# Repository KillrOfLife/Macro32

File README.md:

# Macro32

The Macro32 is a macropad featuring a stm32.
This project was a way for me to learn how to integrate an IC of my choosing on my PCB.
It was also my fist project using kicad

## Take a look

[kicad project](https://kicanvas.org/?github=https://github.com/KillrOfLife/Macro32/blob/main/PCB/macro32.kicad_pro)

## How can I make it myself

Great question!
Go look in the github releases for the latest tag
There you should find the downloads for the PCB production files (aka gerbers)
And the STL's for the case parts if you want that too. (you may need to download the source code)

## How to assemble

For any help assembling this macropad refer to the [build guide](https://github.com/KillrOfLife/Macro32/blob/main/buildguide.md).

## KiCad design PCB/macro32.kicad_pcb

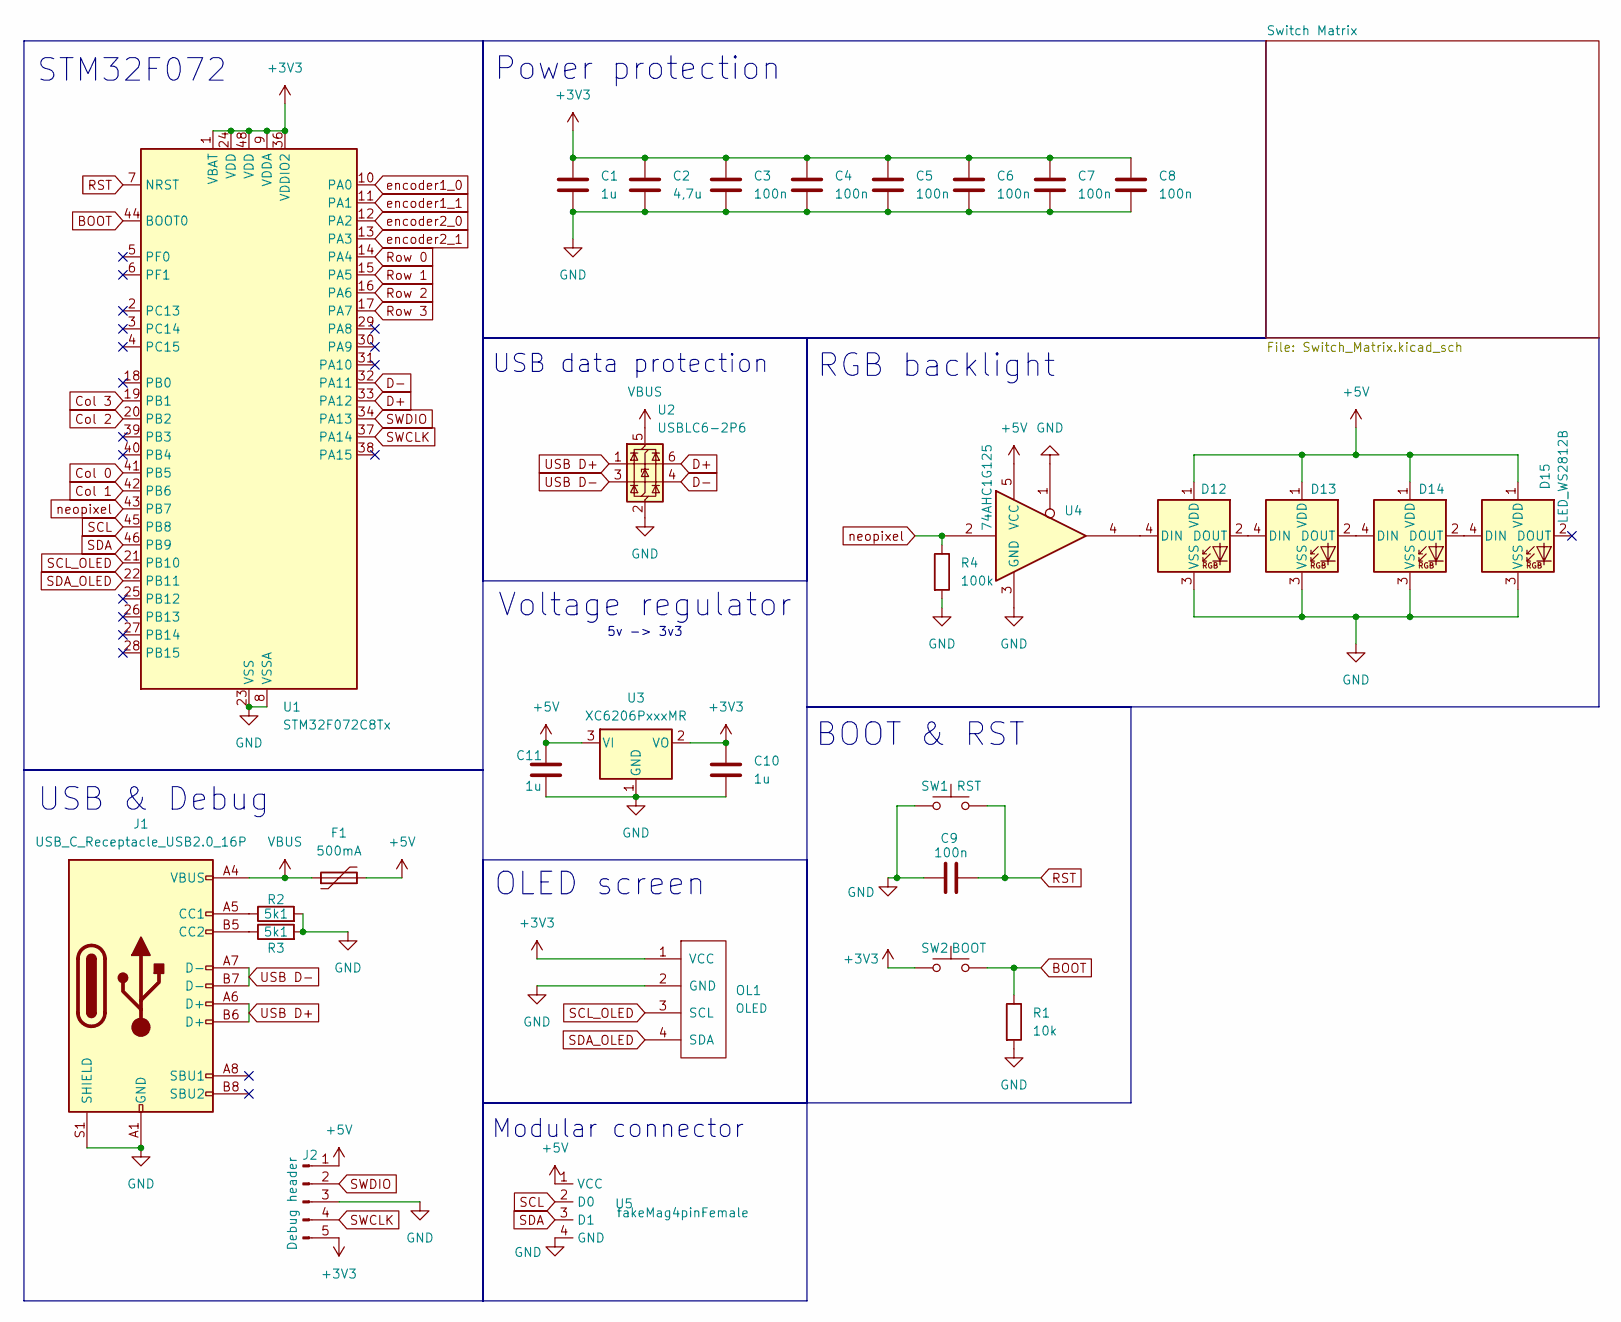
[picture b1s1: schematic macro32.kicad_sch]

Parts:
C1, C10, C11: 1u; LED_0805
C2: 4,7u; LED_0805
C3, C4, C5, C6, C7, C8, C9: 100n; LED_0805
D12, D13, D14, D15: LED_WS2812B
F1: 500mA; Resistor_1206
J1: USB_C_Receptacle_USB2.0_16P; USB_C_Receptacle_GCT_USB4110
J2: Debug header; PinHeader_1x05_P2.54mm_Vertical
OL1: OLED; OLED_128x64
R1: 10k; Resistor_0805
R2, R3: 5k1; Resistor_0805
R4: 100k; Resistor_0805
SW1: RST; SW_SPST_TS-1088-xR020
SW2: BOOT; SW_SPST_TS-1088-xR020
U1: STM32F072C8Tx; LQFP-48_7x7mm_P0.5mm
U2: USBLC6-2P6; SOT-666
U3: XC6206PxxxMR; SOT-23-3
U4: 74AHC1G125; SOT-353_SC-70-5_Handsoldering
U5: fakeMag4pinFemale; fakemag4pin90degFemale

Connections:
+3V3: C1.1, C2.1, C3.1, C4.1, C5.1, C6.1, C7.1, C8.1, C10.1, J2.5, OL1.1 (VCC), SW2.1, U1.1 (VBAT), U1.9 (VDDA), U1.24 (VDD), U1.36 (VDDIO2), U1.48 (VDD), U3.2 (VO)
+5V: C11.1, D12.1 (VDD), D13.1 (VDD), D14.1 (VDD), D15.1 (VDD), F1.2, J2.1, U3.3 (VI), U4.5 (VCC), U5.1 (VCC)
BOOT: R1.1, SW2.2, U1.44 (BOOT0)
Col 0: U1.41 (PB5); also elsewhere on the board
Col 1: U1.42 (PB6); also elsewhere on the board
Col 2: U1.20 (PB2); also elsewhere on the board
Col 3: U1.19 (PB1); also elsewhere on the board
D+: U1.33 (PA12), U2.6 (I/O1)
D-: U1.32 (PA11), U2.4 (I/O2)
GND: C1.2, C2.2, C3.2, C4.2, C5.2, C6.2, C7.2, C8.2, C9.1, C10.2, C11.2, D12.3 (VSS), D13.3 (VSS), D14.3 (VSS), D15.3 (VSS), J1.A1 (GND), J1.A12 (GND), J1.B1 (GND), J1.B12 (GND), J1.S1 (SHIELD), J2.3, OL1.2 (GND), R1.2, R2.2, R3.2, R4.2, SW1.1, U1.8 (VSSA), U1.23 (VSS), U1.35 (VSS), U1.47 (VSS), U2.2 (GND), U3.1 (GND), U4.1, U4.3 (GND), U5.4 (GND); also elsewhere on the board
unnamed: D12.4 (DIN), U4.4
unnamed: D12.2 (DOUT), D13.4 (DIN)
unnamed: D13.2 (DOUT), D14.4 (DIN)
unnamed: D14.2 (DOUT), D15.4 (DIN)
unnamed: J1.A5 (CC1), R2.1
unnamed: J1.B5 (CC2), R3.1
RST: C9.2, SW1.2, U1.7 (NRST)
Row 0: U1.14 (PA4); also elsewhere on the board
Row 1: U1.15 (PA5); also elsewhere on the board
Row 2: U1.16 (PA6); also elsewhere on the board
Row 3: U1.17 (PA7); also elsewhere on the board
SCL: U1.45 (PB8), U5.2 (D0)
SCL_OLED: OL1.3 (SCL), U1.21 (PB10)
SDA: U1.46 (PB9), U5.3 (D1)
SDA_OLED: OL1.4 (SDA), U1.22 (PB11)
SWCLK: J2.4, U1.37 (PA14)
SWDIO: J2.2, U1.34 (PA13)
USB D+: J1.A6 (D+), J1.B6 (D+), U2.1 (I/O1)
USB D-: J1.A7 (D-), J1.B7 (D-), U2.3 (I/O2)
VBUS: F1.1, J1.A4 (VBUS), J1.A9 (VBUS), J1.B4 (VBUS), J1.B9 (VBUS), U2.5 (VBUS)
encoder1_0: U1.10 (PA0); also elsewhere on the board
encoder1_1: U1.11 (PA1); also elsewhere on the board
encoder2_0: U1.12 (PA2); also elsewhere on the board
encoder2_1: U1.13 (PA3); also elsewhere on the board
neopixel: R4.1, U1.43 (PB7), U4.2

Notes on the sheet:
Power protection
STM32F072
5v -> 3v3
RGB backlight
USB & Debug
Modular connector
Voltage regulator
BOOT & RST
OLED screen
USB data protection

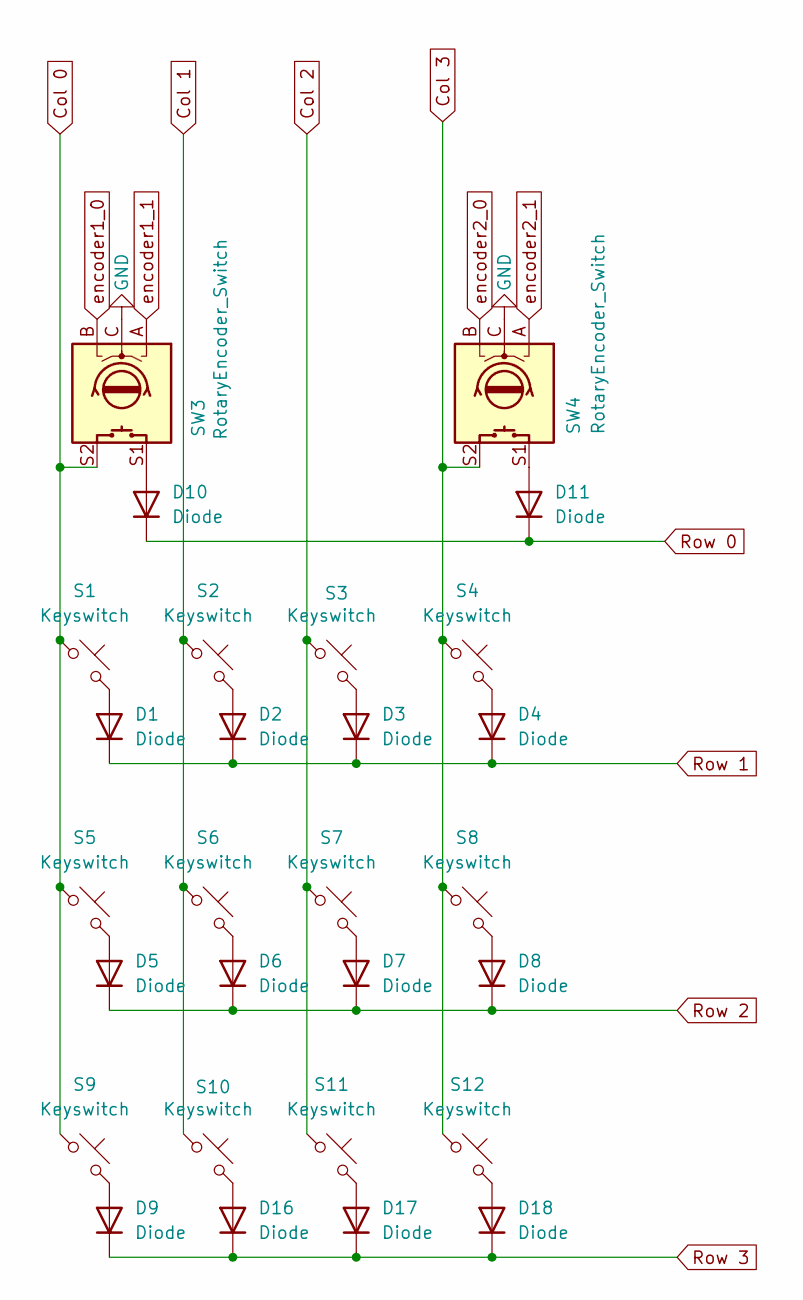
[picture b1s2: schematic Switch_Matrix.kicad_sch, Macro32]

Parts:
D1, D2, D3, D4, D5, D6, D7, D8, D9, D10, D11, D16, D17, D18: Diode; Diode_SOD-123
S1, S2, S3, S4, S5, S6, S7, S8, S9, S10, S11, S12: Keyswitch; Hotswap_MX_1.00u
SW3, SW4: RotaryEncoder_Switch; keyswitch_cherrymx_hotswap_1u_rotary_encoder_ec12

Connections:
Col 0: S1.1, S5.1, S9.1, SW3.S2; also elsewhere on the board
Col 1: S2.1, S6.1, S10.1; also elsewhere on the board
Col 2: S3.1, S7.1, S11.1; also elsewhere on the board
Col 3: S4.1, S8.1, S12.1, SW4.S2; also elsewhere on the board
GND: SW3.C, SW4.C; also elsewhere on the board
unnamed: D1.2 (A), S1.2
unnamed: D2.2 (A), S2.2
unnamed: D3.2 (A), S3.2
unnamed: D4.2 (A), S4.2
unnamed: D5.2 (A), S5.2
unnamed: D6.2 (A), S6.2
unnamed: D7.2 (A), S7.2
unnamed: D8.2 (A), S8.2
unnamed: D9.2 (A), S9.2
unnamed: D10.2 (A), SW3.S1
unnamed: D11.2 (A), SW4.S1
unnamed: D16.2 (A), S10.2
unnamed: D17.2 (A), S11.2
unnamed: D18.2 (A), S12.2
Row 0: D10.1 (K), D11.1 (K); also elsewhere on the board
Row 1: D1.1 (K), D2.1 (K), D3.1 (K), D4.1 (K); also elsewhere on the board
Row 2: D5.1 (K), D6.1 (K), D7.1 (K), D8.1 (K); also elsewhere on the board
Row 3: D9.1 (K), D16.1 (K), D17.1 (K), D18.1 (K); also elsewhere on the board
encoder1_0: SW3.B; also elsewhere on the board
encoder1_1: SW3.A; also elsewhere on the board
encoder2_0: SW4.B; also elsewhere on the board
encoder2_1: SW4.A; also elsewhere on the board

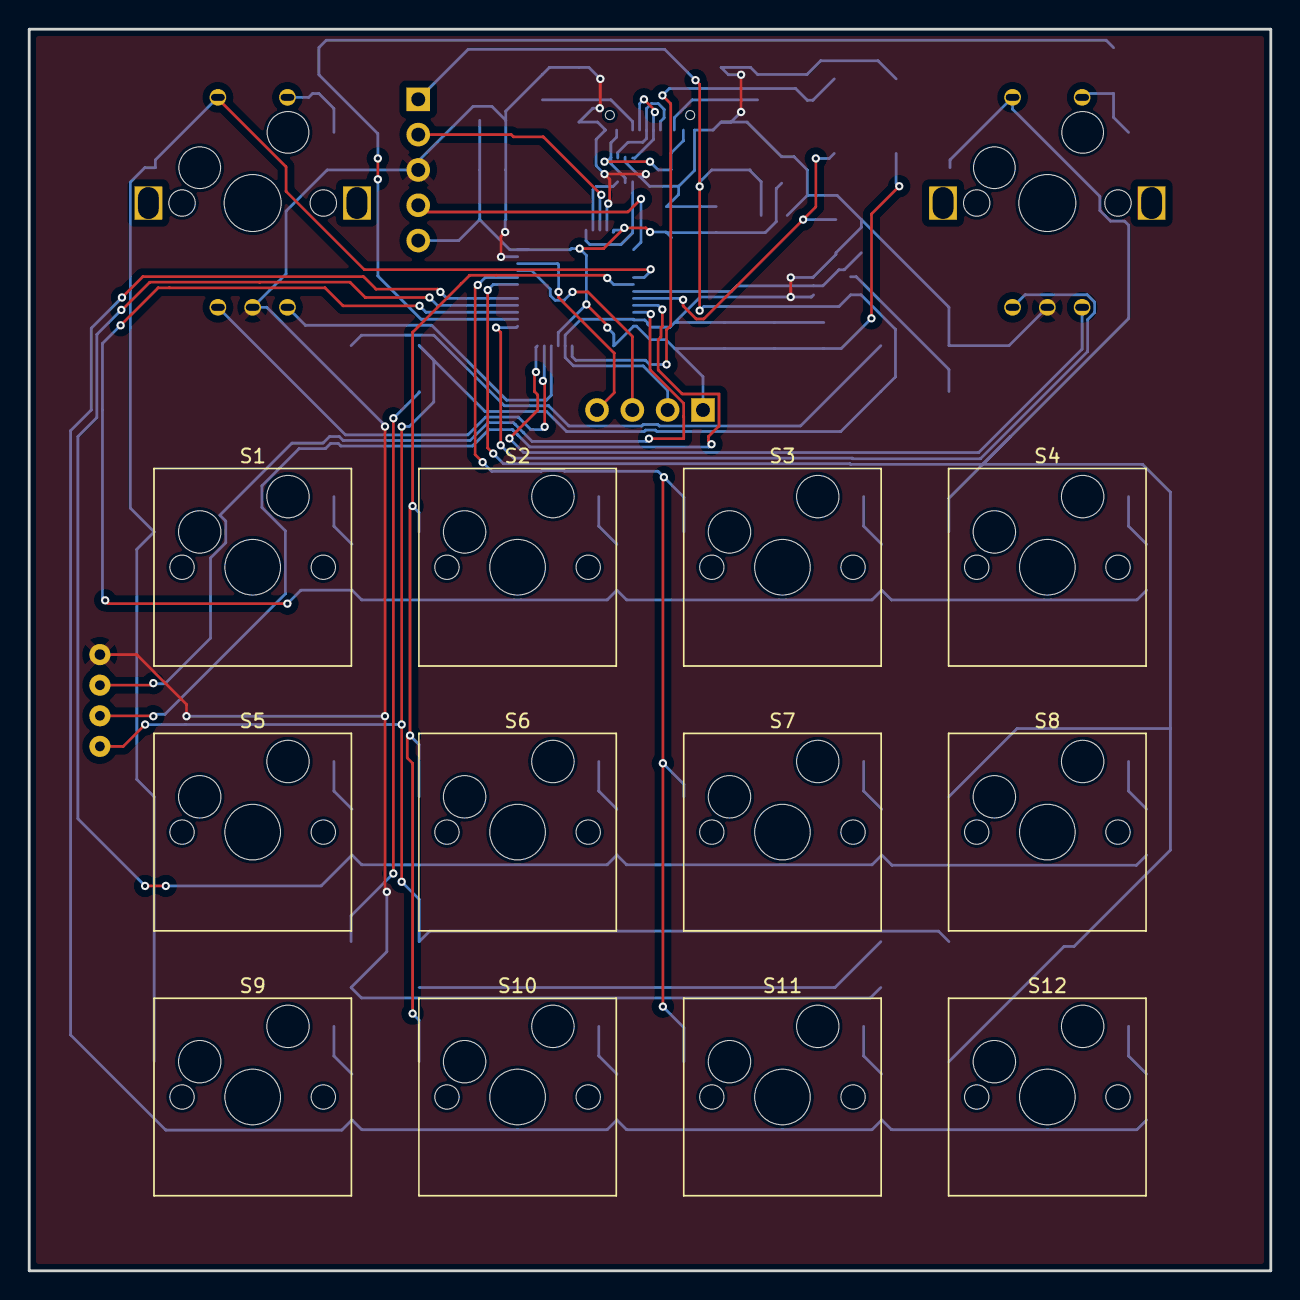
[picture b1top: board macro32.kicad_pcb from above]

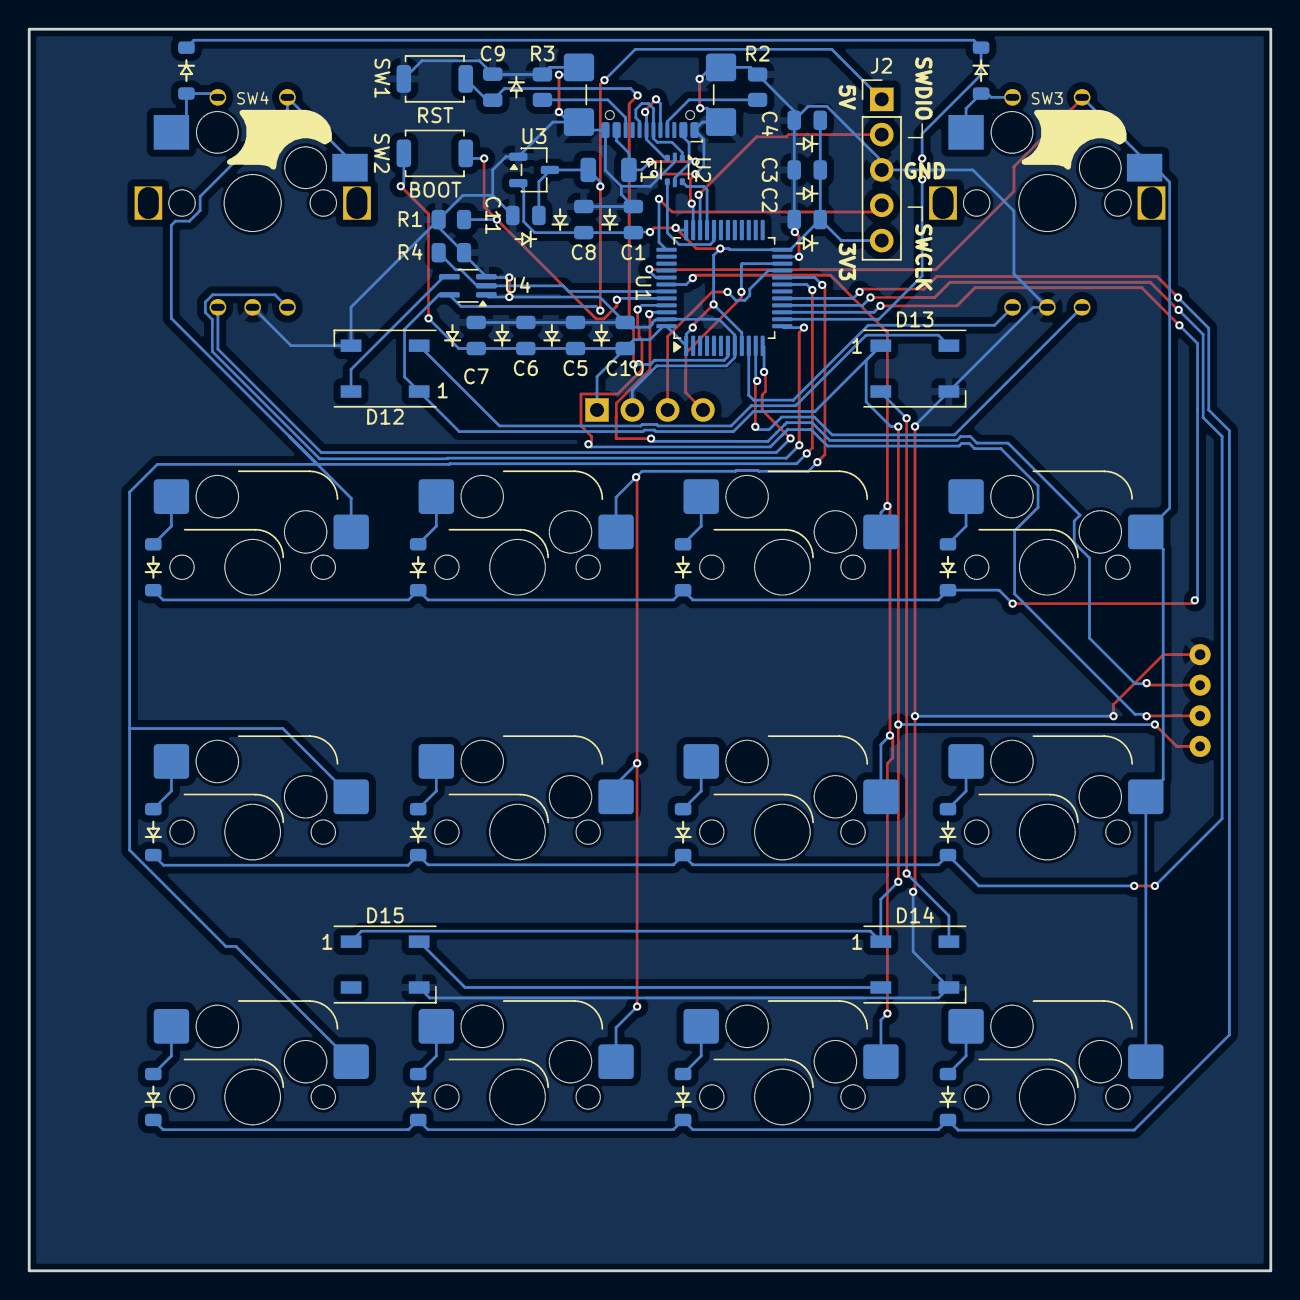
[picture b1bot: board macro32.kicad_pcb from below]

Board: 2 copper layers, 89.3 x 89.3 mm, 58 parts (45 on the bottom side), 49 nets.

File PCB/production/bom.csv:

Designator,Footprint,Quantity,Value,LCSC Part #
C1,LED_0805,1,"4,7u",
"C10, C11, C2",LED_0805,3,1u,
"C3, C4, C5, C6, C7, C8, C9",LED_0805,7,100n,
"D1, D10, D11, D16, D17, D18, D2, D3, D4, D5, D6, D7, D8, D9",Diode_SOD-123,14,Diode,
"D12, D13, D14, D15",LED_WS2812B,4,LED_WS2812B,
F1,Resistor_1206,1,500mA,
J1,USB_C_Receptacle_GCT_USB4110,1,USB_C_Receptacle_USB2.0_16P,
R1,Resistor_0805,1,10k,
"R2, R3",Resistor_0805,2,5k1,
R4,Resistor_0805,1,100k,
"S1, S10, S11, S12, S2, S3, S4, S5, S6, S7, S8, S9",Hotswap_MX_1.00u,12,Keyswitch,
SW1,SW_SPST_TS-1088-xR020,1,RST,
SW2,SW_SPST_TS-1088-xR020,1,boot,
"SW3, SW4",keyswitch_cherrymx_hotswap_1u_rotary_encoder_ec12,2,RotaryEncoder_Switch,
U1,LQFP-48_7x7mm_P0.5mm,1,STM32F072C8Tx,
U2,SOT-666,1,USBLC6-2P6,
U3,SOT-23-3,1,XC6206PxxxMR,
U4,SOT-353_SC-70-5_Handsoldering,1,74AHC1G125,

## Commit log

2025-10-30 Macro32
2025-11-08 V1.1
2025-11-08 Remove obsolete files and added them to .gitignore
2025-11-08 Added OLED_SPI connector for the NICE!view
2025-11-08 Schema for V2 Did some cleanup and seperated the switch matrix to it's own file fixes #1
2025-11-09 Add y-offset to keymap entry in vial.json
2025-11-09 Update OLED_128x64 footprint version and adjust properties
2025-11-09 Adjust PCB layout and added magnetic connector for modularity
2025-11-09 PCB for v2 in the works
2025-11-09 PCB design v2
2025-11-11 added kicad support for nrf52840
